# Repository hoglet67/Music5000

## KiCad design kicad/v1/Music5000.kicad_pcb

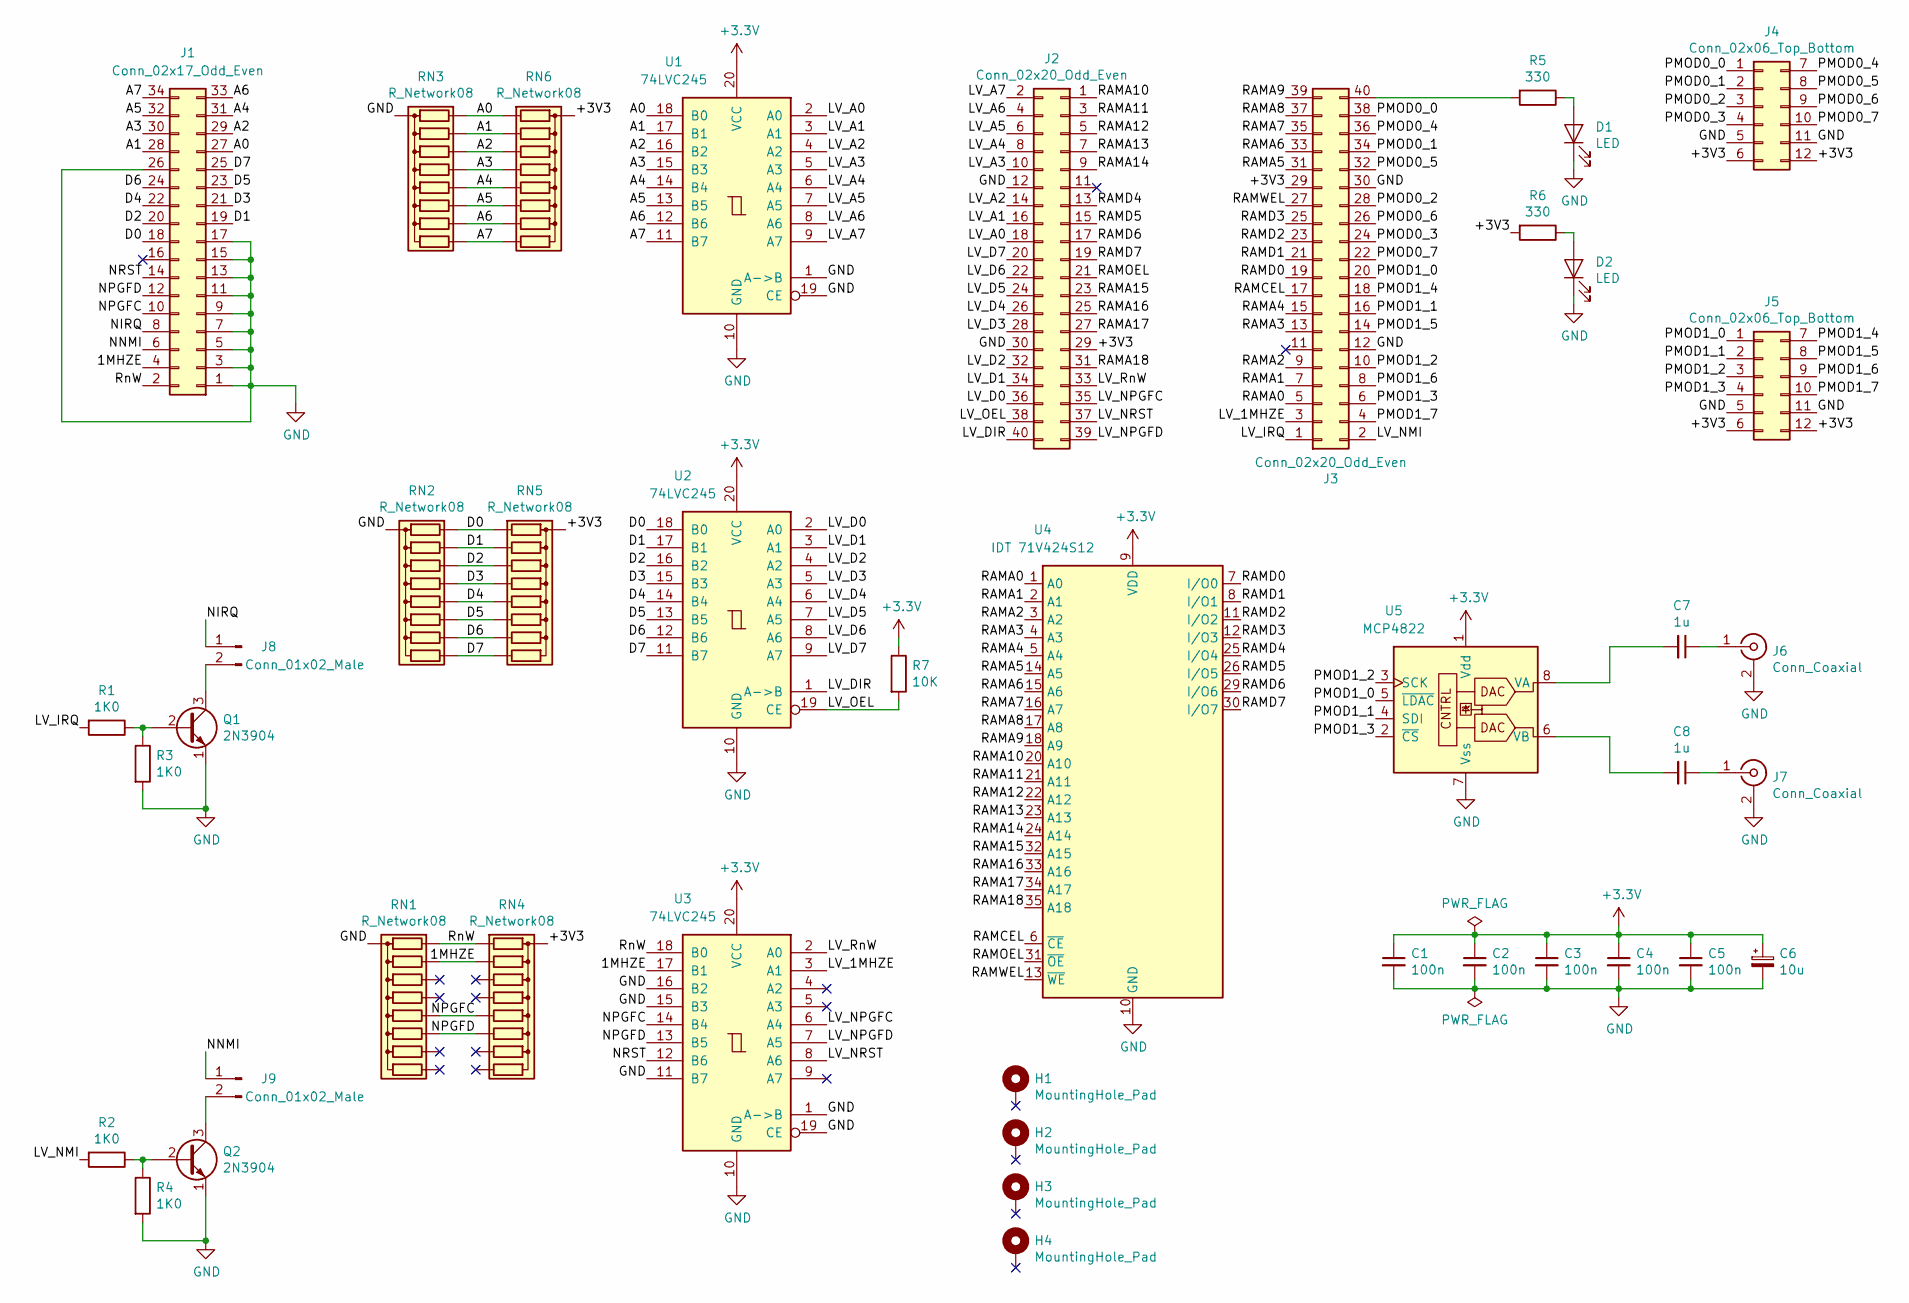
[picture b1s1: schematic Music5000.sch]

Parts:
C1, C2, C3, C4, C5: 100n; C_Axial_L5.1mm_D3.1mm_P10.00mm_Horizontal
C6: 10u; CP_Radial_D5.0mm_P2.50mm
C7, C8: 1u; C_Rect_L7.2mm_W5.5mm_P5.00mm_FKS2_FKP2_MKS2_MKP2
D1, D2: LED; LED_D3.0mm
H1, H2, H3, H4: MountingHole_Pad; MountingHole_3.2mm_M3_Pad
J1: Conn_02x17_Odd_Even; IDC-Header_2x17_P2.54mm_Horizontal_Lock
J2, J3: Conn_02x20_Odd_Even; PinSocket_2x20_P2.54mm_Vertical
J4, J5: Conn_02x06_Top_Bottom; PinSocket_2x06_P2.54mm_Horizontal
J6, J7: Conn_Coaxial; phono
J8, J9: Conn_01x02_Male; PinHeader_1x02_P2.54mm_Vertical
Q1, Q2: 2N3904; TO-92_HandSolder
R1, R2, R3, R4: 1K0; R_Axial_DIN0207_L6.3mm_D2.5mm_P10.16mm_Horizontal
R5, R6: 330; R_Axial_DIN0207_L6.3mm_D2.5mm_P10.16mm_Horizontal
R7: 10K; R_Axial_DIN0207_L6.3mm_D2.5mm_P10.16mm_Horizontal
RN1, RN2, RN3, RN4, RN5, RN6: R_Network08; R_Array_SIP9
U1, U2, U3: 74LVC245; DIP-20_W7.62mm_Socket
U4: IDT 71V424S12; SOJ-36_10.16x23.49mm_P1.27mm
U5: MCP4822; DIP-8_W7.62mm_Socket

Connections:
/1MHZE: J1.4, RN1.3 (R2), RN4.3 (R2), U3.17 (B1)
/A0: J1.27, RN3.2 (R1), RN6.2 (R1), U1.18 (B0)
/A1: J1.28, RN3.3 (R2), RN6.3 (R2), U1.17 (B1)
/A2: J1.29, RN3.4 (R3), RN6.4 (R3), U1.16 (B2)
/A3: J1.30, RN3.5 (R4), RN6.5 (R4), U1.15 (B3)
/A4: J1.31, RN3.6 (R5), RN6.6 (R5), U1.14 (B4)
/A5: J1.32, RN3.7 (R6), RN6.7 (R6), U1.13 (B5)
/A6: J1.33, RN3.8 (R7), RN6.8 (R7), U1.12 (B6)
/A7: J1.34, RN3.9 (R8), RN6.9 (R8), U1.11 (B7)
/D0: J1.18, RN2.2 (R1), RN5.2 (R1), U2.18 (B0)
/D1: J1.19, RN2.3 (R2), RN5.3 (R2), U2.17 (B1)
/D2: J1.20, RN2.4 (R3), RN5.4 (R3), U2.16 (B2)
/D3: J1.21, RN2.5 (R4), RN5.5 (R4), U2.15 (B3)
/D4: J1.22, RN2.6 (R5), RN5.6 (R5), U2.14 (B4)
/D5: J1.23, RN2.7 (R6), RN5.7 (R6), U2.13 (B5)
/D6: J1.24, RN2.8 (R7), RN5.8 (R7), U2.12 (B6)
/D7: J1.25, RN2.9 (R8), RN5.9 (R8), U2.11 (B7)
/LV_1MHZE: J3.3, U3.3 (A1)
/LV_A0: J2.18, U1.2 (A0)
/LV_A1: J2.16, U1.3 (A1)
/LV_A2: J2.14, U1.4 (A2)
/LV_A3: J2.10, U1.5 (A3)
/LV_A4: J2.8, U1.6 (A4)
/LV_A5: J2.6, U1.7 (A5)
/LV_A6: J2.4, U1.8 (A6)
/LV_A7: J2.2, U1.9 (A7)
/LV_D0: J2.36, U2.2 (A0)
/LV_D1: J2.34, U2.3 (A1)
/LV_D2: J2.32, U2.4 (A2)
/LV_D3: J2.28, U2.5 (A3)
/LV_D4: J2.26, U2.6 (A4)
/LV_D5: J2.24, U2.7 (A5)
/LV_D6: J2.22, U2.8 (A6)
/LV_D7: J2.20, U2.9 (A7)
/LV_DIR: J2.40, U2.1 (A->B)
/LV_IRQ: J3.1, R1.2
/LV_NMI: J3.2, R2.2
/LV_NPGFC: J2.35, U3.6 (A4)
/LV_NPGFD: J2.39, U3.7 (A5)
/LV_NRST: J2.37, U3.8 (A6)
/LV_OEL: J2.38, R7.2, U2.19 (CE)
/LV_RnW: J2.33, U3.2 (A0)
/NIRQ: J1.8, J8.1
/NNMI: J1.6, J9.1
/NPGFC: J1.10, RN1.6 (R5), RN4.6 (R5), U3.14 (B4)
/NPGFD: J1.12, RN1.7 (R6), RN4.7 (R6), U3.13 (B5)
/NRST: J1.14, U3.12 (B6)
/PMOD0_0: J3.38, J4.1
/PMOD0_1: J3.34, J4.2
/PMOD0_2: J3.28, J4.3
/PMOD0_3: J3.24, J4.4
/PMOD0_4: J3.36, J4.7
/PMOD0_5: J3.32, J4.8
/PMOD0_6: J3.26, J4.9
/PMOD0_7: J3.22, J4.10
/PMOD1_0: J3.20, J5.1, U5.5 (~LDAC)
/PMOD1_1: J3.16, J5.2, U5.4 (SDI)
/PMOD1_2: J3.10, J5.3, U5.3 (SCK)
/PMOD1_3: J3.6, J5.4, U5.2 (~CS)
/PMOD1_4: J3.18, J5.7
/PMOD1_5: J3.14, J5.8
/PMOD1_6: J3.8, J5.9
/PMOD1_7: J3.4, J5.10
/RAMA0: J3.5, U4.1 (A0)
/RAMA1: J3.7, U4.2 (A1)
/RAMA2: J3.9, U4.3 (A2)
/RAMA3: J3.13, U4.4 (A3)
/RAMA4: J3.15, U4.5 (A4)
/RAMA5: J3.31, U4.14 (A5)
/RAMA6: J3.33, U4.15 (A6)
/RAMA7: J3.35, U4.16 (A7)
/RAMA8: J3.37, U4.17 (A8)
/RAMA9: J3.39, U4.18 (A9)
/RAMA10: J2.1, U4.20 (A10)
/RAMA11: J2.3, U4.21 (A11)
/RAMA12: J2.5, U4.22 (A12)
/RAMA13: J2.7, U4.23 (A13)
/RAMA14: J2.9, U4.24 (A14)
/RAMA15: J2.23, U4.32 (A15)
/RAMA16: J2.25, U4.33 (A16)
/RAMA17: J2.27, U4.34 (A17)
/RAMA18: J2.31, U4.35 (A18)
/RAMCEL: J3.17, U4.6 (~CE)
/RAMD0: J3.19, U4.7 (I/O0)
/RAMD1: J3.21, U4.8 (I/O1)
/RAMD2: J3.23, U4.11 (I/O2)
/RAMD3: J3.25, U4.12 (I/O3)
/RAMD4: J2.13, U4.25 (I/O4)
/RAMD5: J2.15, U4.26 (I/O5)
/RAMD6: J2.17, U4.29 (I/O6)
/RAMD7: J2.19, U4.30 (I/O7)
/RAMOEL: J2.21, U4.31 (~OE)
/RAMWEL: J3.27, U4.13 (~WE)
/RnW: J1.2, RN1.2 (R1), RN4.2 (R1), U3.18 (B0)
GND: C1.2, C2.2, C3.2, C4.2, C5.2, C6.2, D1.1 (K), D2.1 (K), J1.1, J1.3, J1.5, J1.7, J1.9, J1.11, J1.13, J1.15, J1.17, J1.26, J2.12, J2.30, J3.12, J3.30, J4.5, J4.11, J5.5, J5.11, J6.2 (Ext), J7.2 (Ext), Q1.1 (E), Q2.1 (E), R3.2, R4.2, RN1.1 (common), RN2.1 (common), RN3.1 (common), U1.1 (A->B), U1.10 (GND), U1.19 (CE), U2.10 (GND), U3.1 (A->B), U3.10 (GND), U3.11 (B7), U3.15 (B3), U3.16 (B2), U3.19 (CE), U4.10 (GND), U4.28 (GND), U5.7 (Vss)
unnamed: C7.1, J6.1 (In)
unnamed: C7.2, U5.8 (VA)
unnamed: C8.1, J7.1 (In)
unnamed: C8.2, U5.6 (VB)
unnamed: D1.2 (A), R5.1
unnamed: D2.2 (A), R6.1
unnamed: J3.40, R5.2
unnamed: J8.2, Q1.3 (C)
unnamed: J9.2, Q2.3 (C)
unnamed: Q1.2 (B), R1.1, R3.1
unnamed: Q2.2 (B), R2.1, R4.1

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
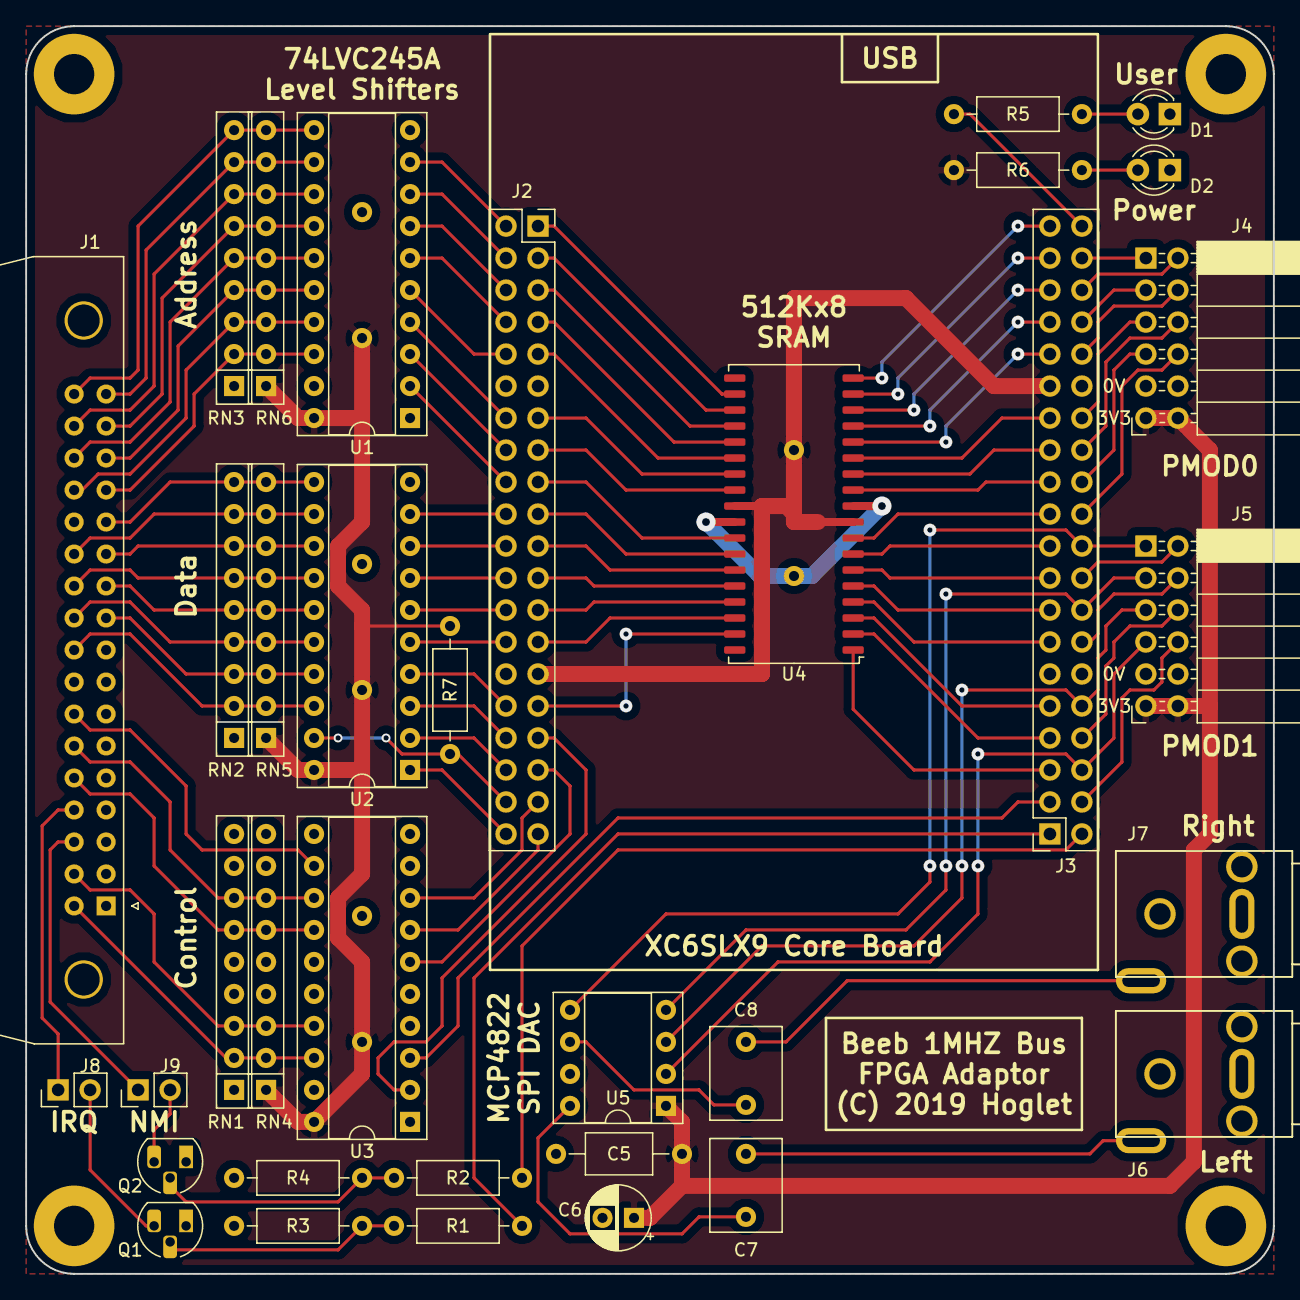
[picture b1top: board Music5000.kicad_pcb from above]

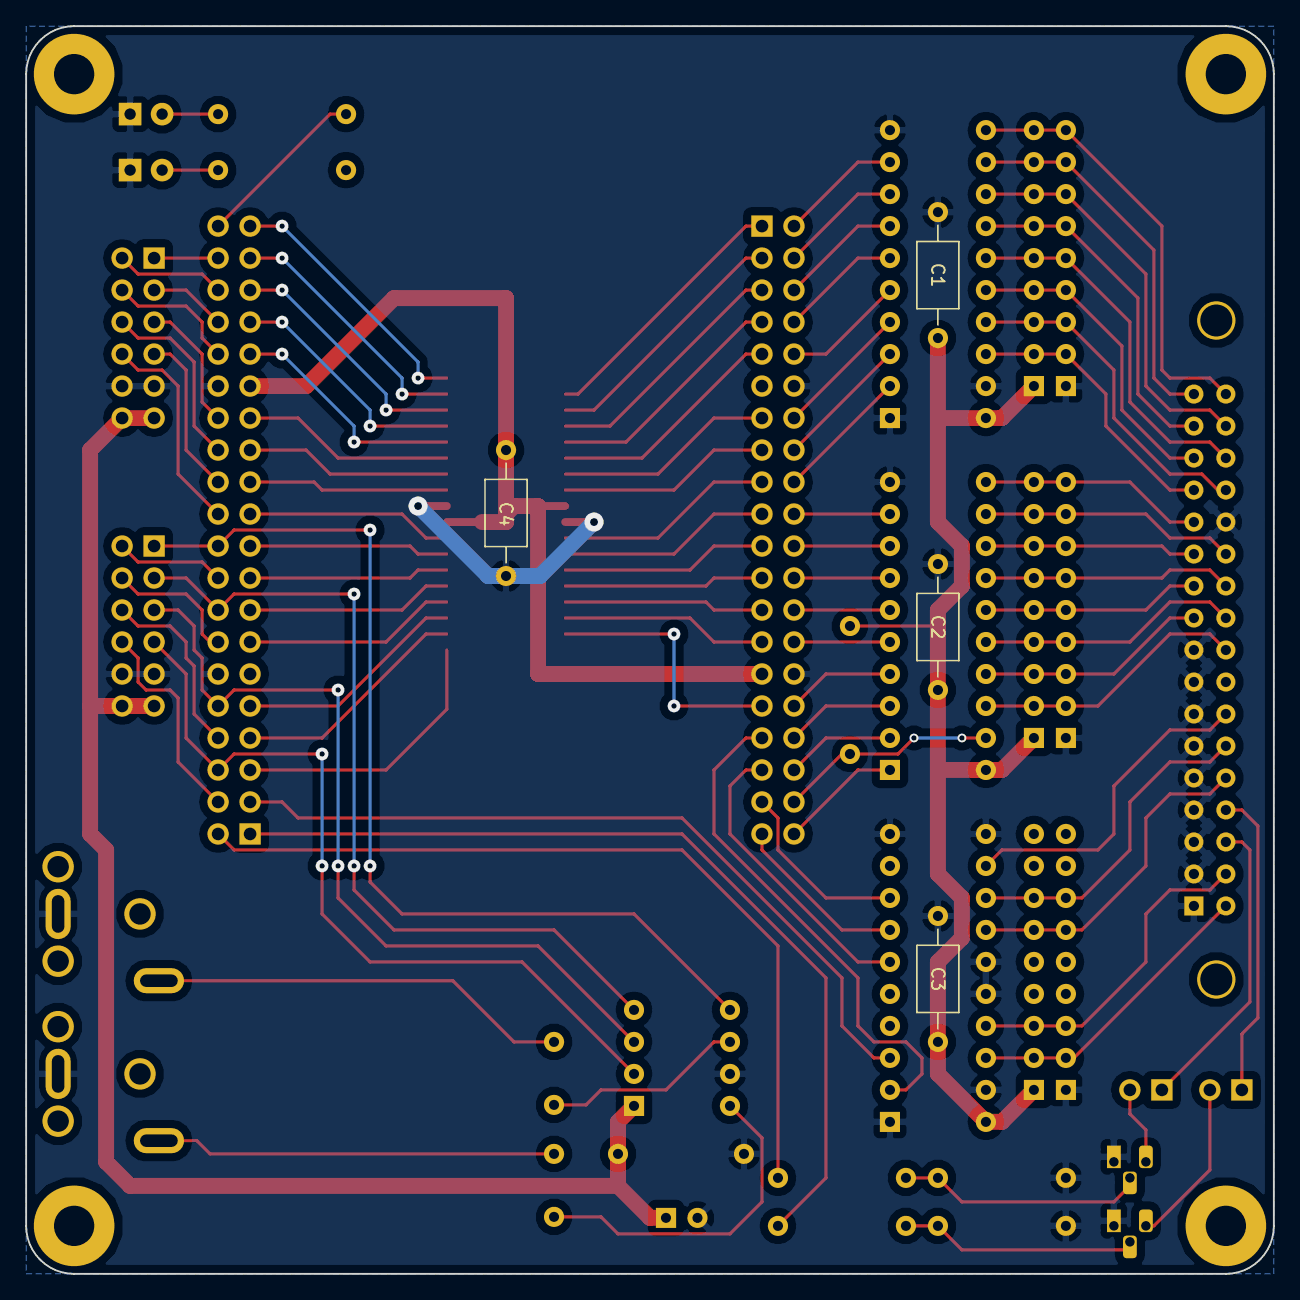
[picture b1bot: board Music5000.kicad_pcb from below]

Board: 2 copper layers, 99.1 x 99.1 mm, 43 parts (4 on the bottom side), 107 nets.

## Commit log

2014-11-20 Fixed a couple of small bugs, and updated to use an external MCP4822 12-bit DAC
2015-03-29 Added Screen Dumps of the Wave Images
2019-03-01 Refactor to better suppoer several targets (inc BeebFpga)
2019-03-01 Added v1 of 1MHz Bus FPGA Adapter PCB
2019-03-02 Added dout_oel; Hardware is deselected on reset
2019-03-02 Updated reset behaviour to match real M5K, including writing to wave ram
2019-03-02 Made id a paramater with a view to the Music3000 expander
2019-03-02 Music5000_gop: Fixed very incorrect clock frequency
2019-03-02 Music5000SpiDac module now includes a Music 3000 as well
2019-03-03 GOP: Added SW1 and SW2 to Mute the 5K/3K audio
2019-03-05 PCB: Added switches
2019-03-05 PCB: Added manufacturing data
2019-03-06 Fixed incorrect case of module name
2019-03-06 Fixed incorrect clke polarity (both seem to work though)
2019-03-06 Added Owl Logo demo via 1MHz Bus
2019-03-06 Added .gitignore
2019-03-07 Bus Adapter PCB now in Beeb1MHzFpga project
2019-03-07 Owl Logo now in Beeb1MHzFpga project
2019-03-07 Added OwlRom into LX9 Build
2019-03-23 Enabled IRQ in LX9 Build
2019-03-23 Increased Config Clock to 26MHz in LX9 Build
2019-05-01 Updated LX9 Build for V2 of the FPGA Adapter (V1 = old)
2019-05-01 Added Creative Commons BY-NC-SA license
2019-05-05 Remove RSTn from LED, so only SW1 and SW2 affect it
2019-05-05 Added binary release of Music5000_lx9core
2019-06-10 Dom JIM API tests and fixes
    Make OWL logo boot user select able at boot (hold SW1)
    FIX: only enable data buffer for reads when necessary - was clobbering all other FRED/JIM devices
2019-06-10 Use PMOD2(3) to disable owl when jumpered to ground
2019-06-10 Reading FCFF return inverted value (when selected)
2019-06-10 Update OwlRom, and include mode 7 check
2019-06-10 Add design the lx9core gets shipped with
2019-06-10 Updated binary release to latest version
2019-06-11 Owl Logo: test for soft break as early as possible
2019-06-11 Owl Logo: Enable boot code when FCFF=00
2023-10-06 Synchronise amplitude changes with waveform zero crossings
2023-10-13 Connect clk6en to the RAM clock enables
2023-10-13 Whitespace - reformat VHDL
2023-10-13 Added S/PDIF output to Music5000SpiDac
2023-10-14 Added a 3rd order butterworth output filter (uses a 19x25 multiplier)
2023-10-14 Fixed some bugs in the iir filter (found with simulation)
2023-10-14 Check in iir_filter step response simulation
2023-10-15 refactor iir filter (work in progress)
2023-10-17 iir_filter simulation - show analog waveforms in gtkwave
2023-10-17 Push fractional gain into coefficients
2023-10-17 Swap L/R channels on S/PDIF output
2025-01-31 Added clken input to spdif_serializer

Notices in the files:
kicad/v1/Music5000.kicad_pcb:
(C) 2019 Hoglet
